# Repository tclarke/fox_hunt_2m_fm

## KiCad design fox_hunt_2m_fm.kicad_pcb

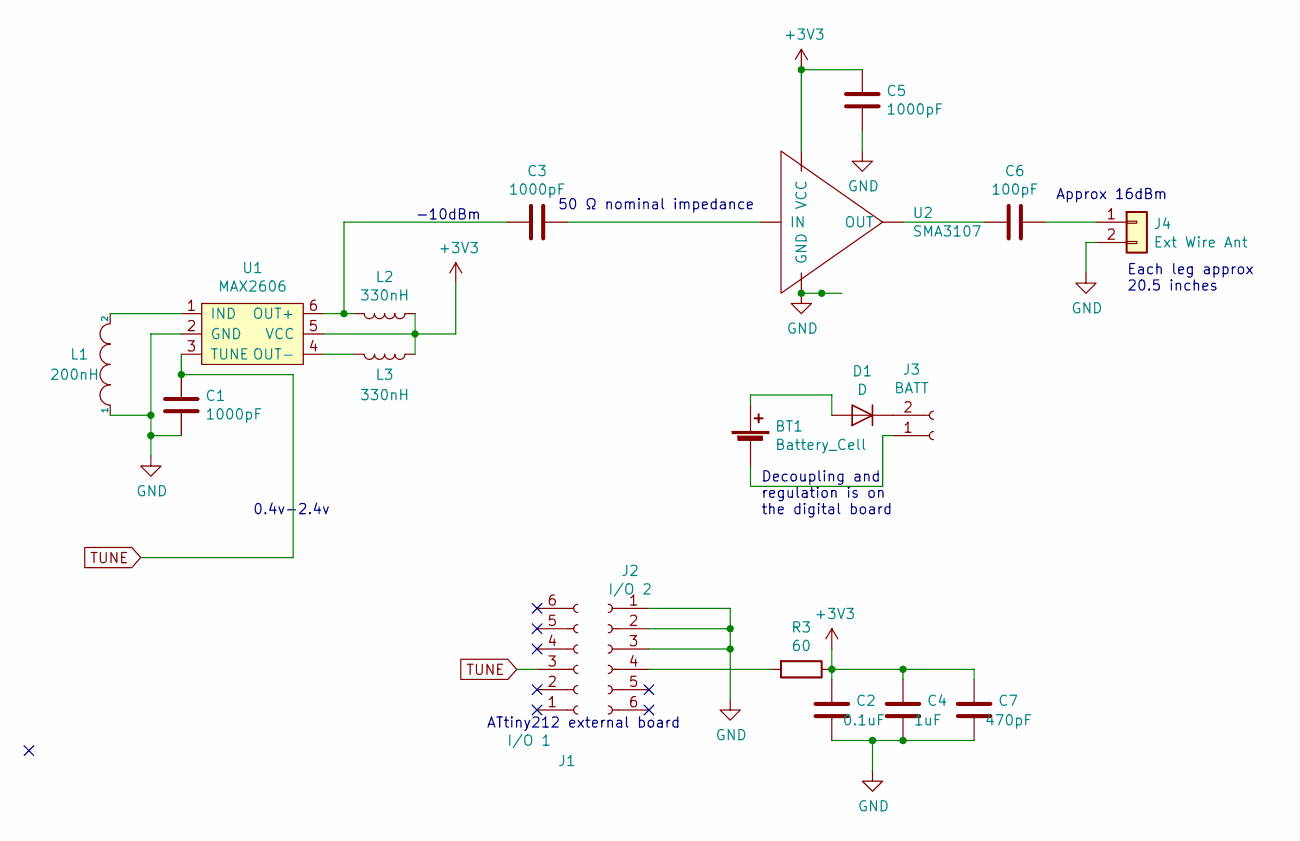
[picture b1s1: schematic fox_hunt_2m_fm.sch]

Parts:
BT1: Battery_Cell; BatteryHolder_Keystone_3034_1x20mm
C1, C3, C5: 1000pF; C_1206_3216Metric_Pad1.33x1.80mm_HandSolder
C2: 0.1uF; C_1206_3216Metric_Pad1.33x1.80mm_HandSolder
C4: 1uF; C_1206_3216Metric_Pad1.33x1.80mm_HandSolder
C6: 100pF; C_1206_3216Metric_Pad1.33x1.80mm_HandSolder
C7: 470pF; C_1206_3216Metric_Pad1.42x1.75mm_HandSolder
D1: D; D_DO-35_SOD27_P7.62mm_Horizontal
J1: I/O 1; PinHeader_1x06_P2.54mm_Vertical
J2: I/O 2; PinHeader_1x06_P2.54mm_Vertical
J3: BATT; PinHeader_1x02_P2.54mm_Vertical
J4: Ext Wire Ant; SolderWire-0.1sqmm_1x02_P3.6mm_D0.4mm_OD1mm_Relief
L1: 200nH; L_0805_2012Metric_Pad1.05x1.20mm_HandSolder
L2, L3: 330nH; L_1008_2520Metric
R3: 60; R_1206_3216Metric_Pad1.30x1.75mm_HandSolder
U1: MAX2606; SOT-23-6
U2: SMA3107; SOT-363_SC-70-6

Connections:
+3V3: C2.1, C4.1, C5.2, C7.1, L2.1, L3.1, R3.1, U1.5 (VCC), U2.1 (VCC)
GND: C1.1, C2.2, C4.2, C5.1, C7.2, J2.1, J2.2, J2.3, J4.2, L1.1, U1.2 (GND), U2.2 (GND), U2.4 (GND), U2.5 (GND)
unnamed: BT1.1 (+), D1.2 (A)
unnamed: BT1.2 (-), J3.1
unnamed: C3.1, U2.6 (IN)
unnamed: C3.2, L2.2, U1.6 (OUT+)
unnamed: C6.1, J4.1
unnamed: C6.2, U2.3 (OUT)
unnamed: D1.1 (K), J3.2
unnamed: J2.4, R3.2
unnamed: L1.2, U1.1 (IND)
unnamed: L3.2, U1.4 (OUT-)
TUNE: C1.2, J1.3, U1.3 (TUNE)

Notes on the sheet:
50 Ω nominal impedance
-10dBm
ATtiny212 external board
Approx 16dBm
0.4v-2.4v
Decoupling and regulation is on the digital board
Each leg approx 20.5 inches

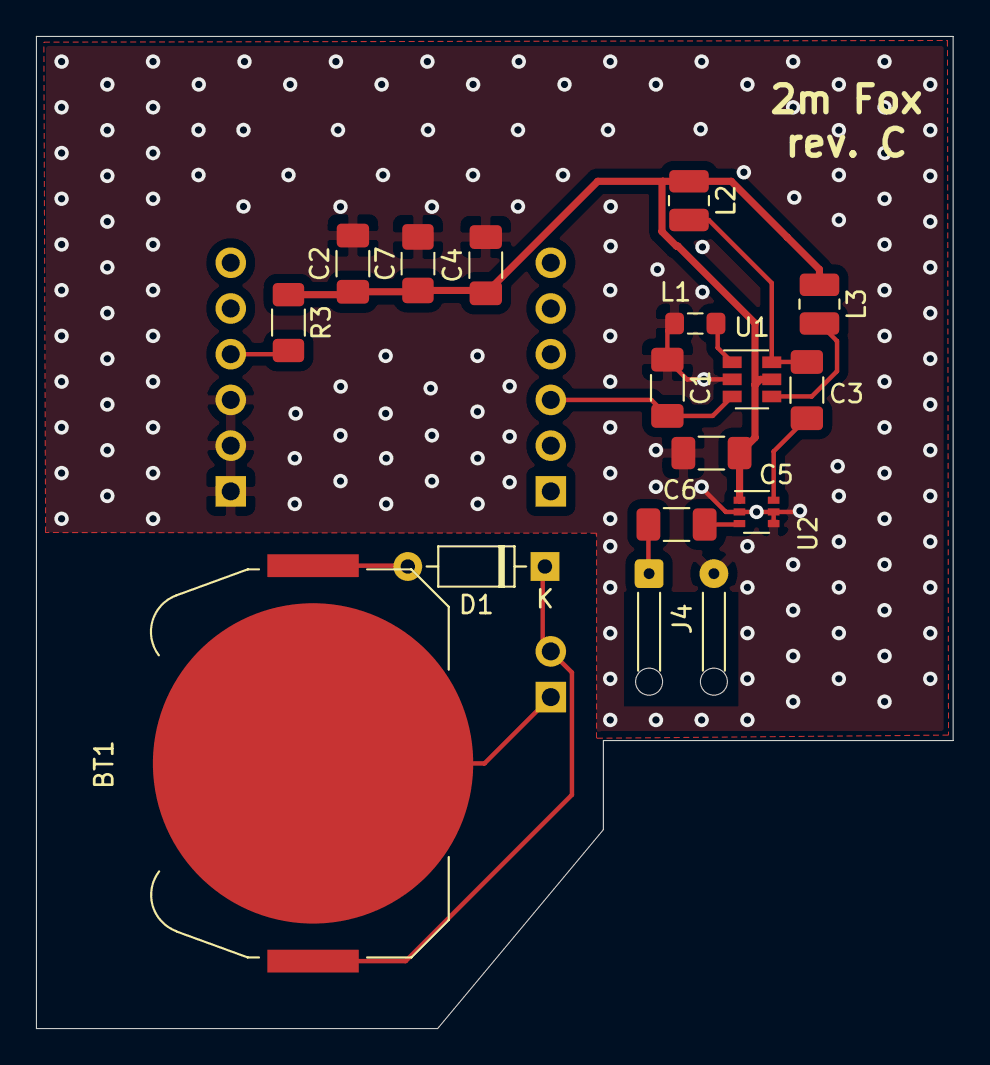
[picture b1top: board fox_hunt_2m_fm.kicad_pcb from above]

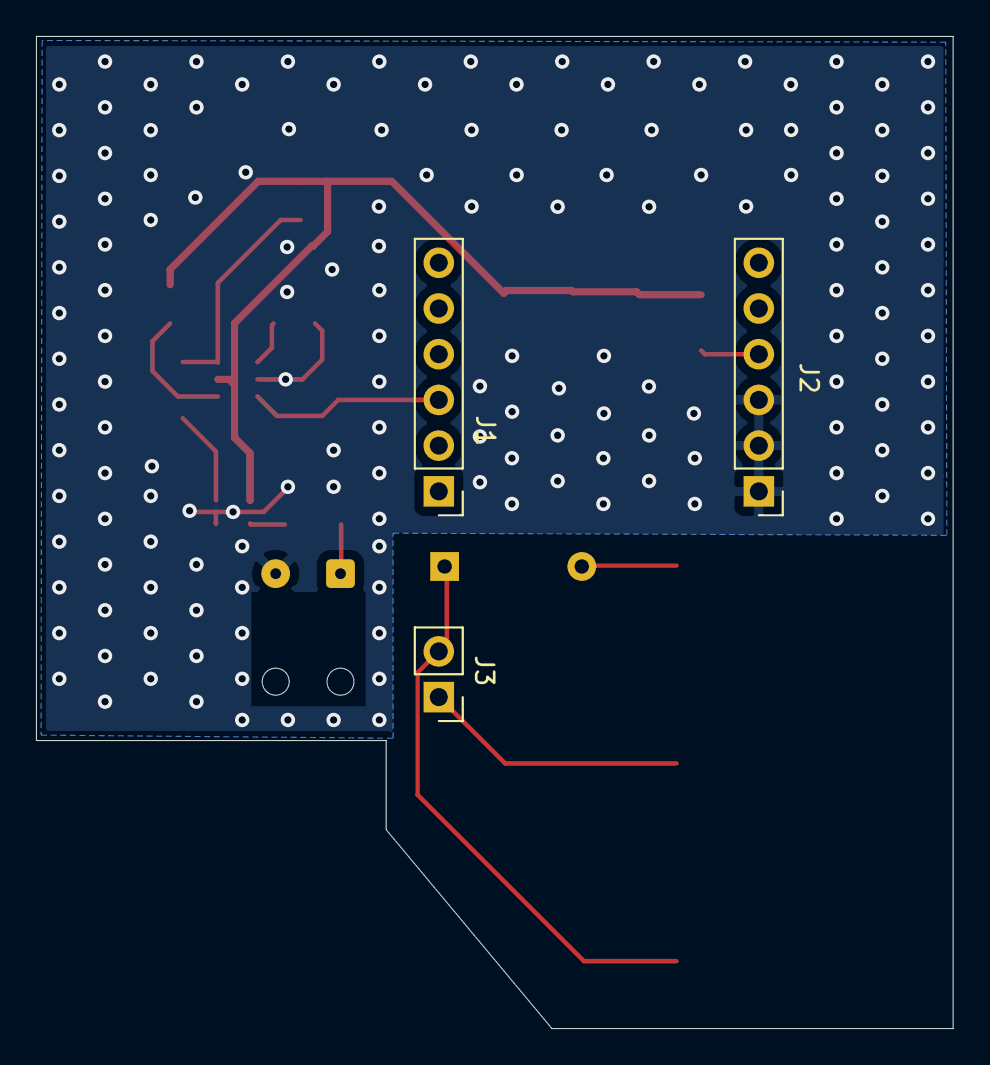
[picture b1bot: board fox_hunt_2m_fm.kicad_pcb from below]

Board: 2 copper layers, 50.9 x 55.1 mm, 19 parts (3 on the bottom side), 13 nets.

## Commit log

2021-05-19 Initial
2021-05-19 Add 3d step view
2021-05-28 Rev B
2021-06-28 Board and schematic Rev. C
    Use IO line to directly power analog section.
    Remove power MOSFET as it's not needed.
    Add additional filter cap.
    Rearrange PCB to account for above.
    Add antenna length to silkscreen.
